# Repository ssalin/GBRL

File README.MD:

Documentation for Airquality platform can be found here

https://docs.google.com/document/d/1oFnARjLuFHp-5nVdnFOoGYGBi9iJlXXOtEU-Aas6cns/edit?usp=sharing

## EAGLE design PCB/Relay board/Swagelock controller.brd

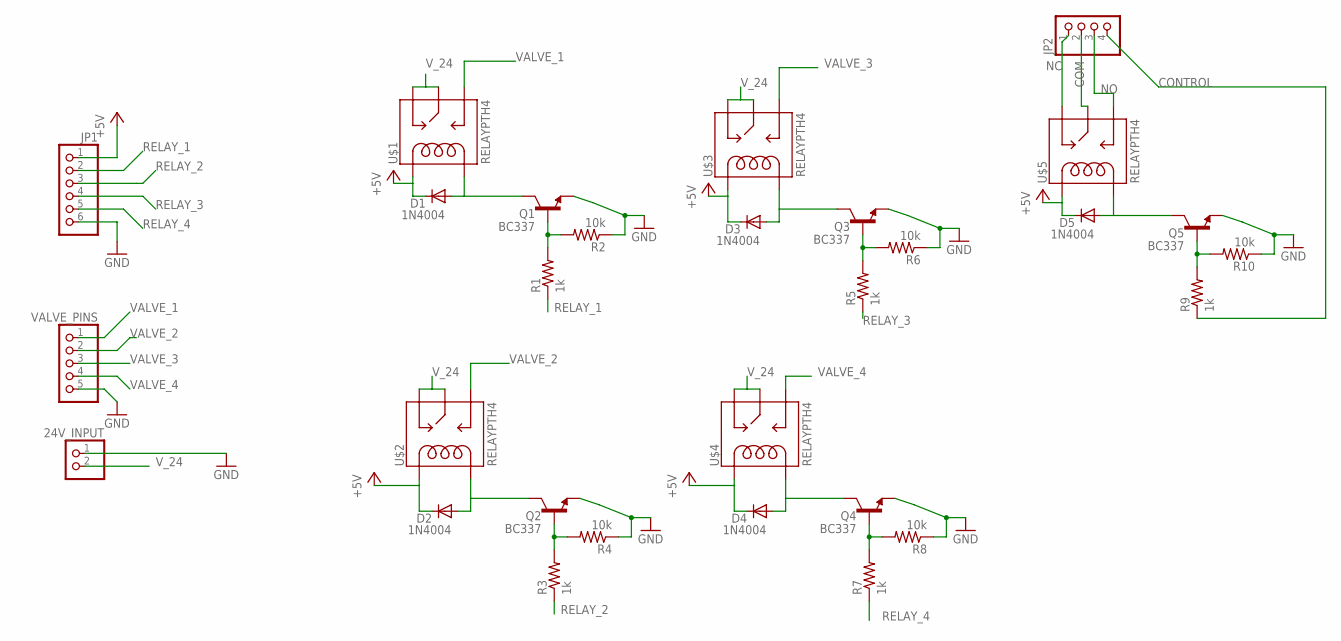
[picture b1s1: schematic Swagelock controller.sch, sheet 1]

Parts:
24V_INPUT: PINHD-1X2; 1X02
D1, D2, D3, D4, D5: 1N4004; DO41-10
JP1: PINHD-1X6; 1X06
JP2: PINHD-1X4; 1X04
Q1, Q2, Q3, Q4, Q5: BC337; TO92
R1, R3, R5, R7, R9: 1k; 0204/5
R2, R4, R6, R8, R10: 10k; 0204/5
U$1, U$2, U$3, U$4, U$5: RELAYPTH4; RELAY-JZC
VALVE_PINS: PINHD-1X5; 1X05

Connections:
+5V: D1.C, D2.C, D3.C, D4.C, D5.C, JP1.1, U$1.5 (COIL1), U$2.5 (COIL1), U$3.5 (COIL1), U$4.5 (COIL1), U$5.5 (COIL1)
COM: JP2.2, U$5.4 (MAIN)
CONTROL: JP2.4, R9.1
GND: 24V_INPUT.1, JP1.6, Q1.1 (E), Q2.1 (E), Q3.1 (E), Q4.1 (E), Q5.1 (E), R2.1, R4.1, R6.1, R8.1, R10.1, VALVE_PINS.5
unnamed: Q1.2 (B), R1.2, R2.2
unnamed: D1.A, Q1.3 (C), U$1.1 (COIL2)
unnamed: Q2.2 (B), R3.2, R4.2
unnamed: D2.A, Q2.3 (C), U$2.1 (COIL2)
unnamed: Q3.2 (B), R5.2, R6.2
unnamed: D3.A, Q3.3 (C), U$3.1 (COIL2)
unnamed: Q4.2 (B), R7.2, R8.2
unnamed: D4.A, Q4.3 (C), U$4.1 (COIL2)
unnamed: Q5.2 (B), R9.2, R10.2
unnamed: D5.A, Q5.3 (C), U$5.1 (COIL2)
NC: JP2.1, U$5.2 (NC)
NO: JP2.3, U$5.3 (NO)
RELAY_1: JP1.2, R1.1
RELAY_2: JP1.3, R3.1
RELAY_3: JP1.4, R5.1
RELAY_4: JP1.5, R7.1
VALVE_1: U$1.3 (NO), VALVE_PINS.1
VALVE_2: U$2.3 (NO), VALVE_PINS.2
VALVE_3: U$3.3 (NO), VALVE_PINS.3
VALVE_4: U$4.3 (NO), VALVE_PINS.4
V_24: 24V_INPUT.2, U$1.2 (NC), U$1.4 (MAIN), U$2.2 (NC), U$2.4 (MAIN), U$3.2 (NC), U$3.4 (MAIN), U$4.2 (NC), U$4.4 (MAIN)

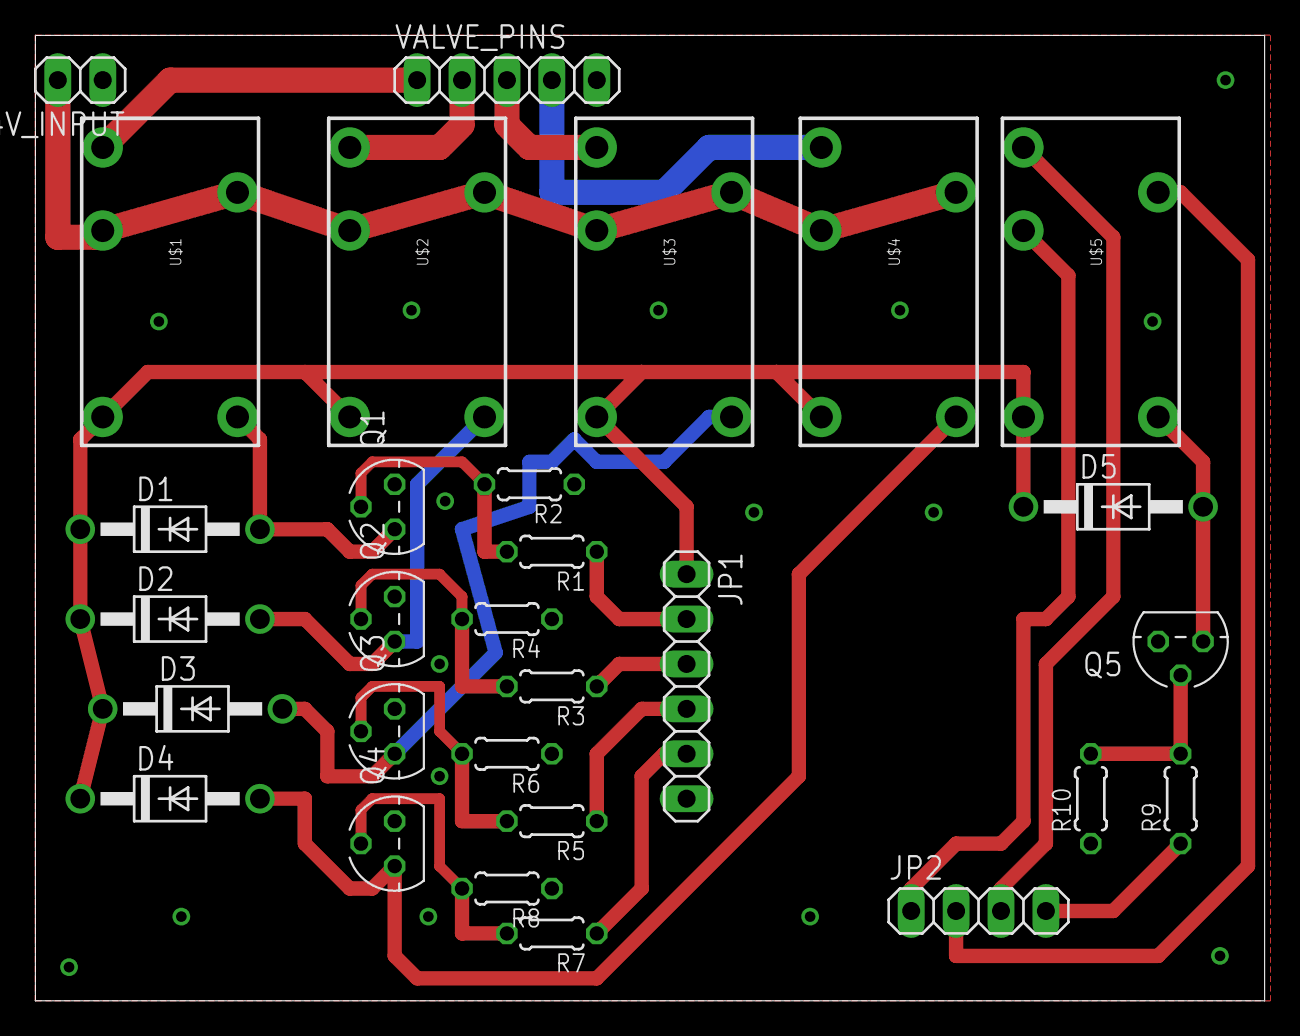
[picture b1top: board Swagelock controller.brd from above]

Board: 2 copper layers, 69.5 x 54.6 mm, 29 parts (0 on the bottom side), 25 nets.

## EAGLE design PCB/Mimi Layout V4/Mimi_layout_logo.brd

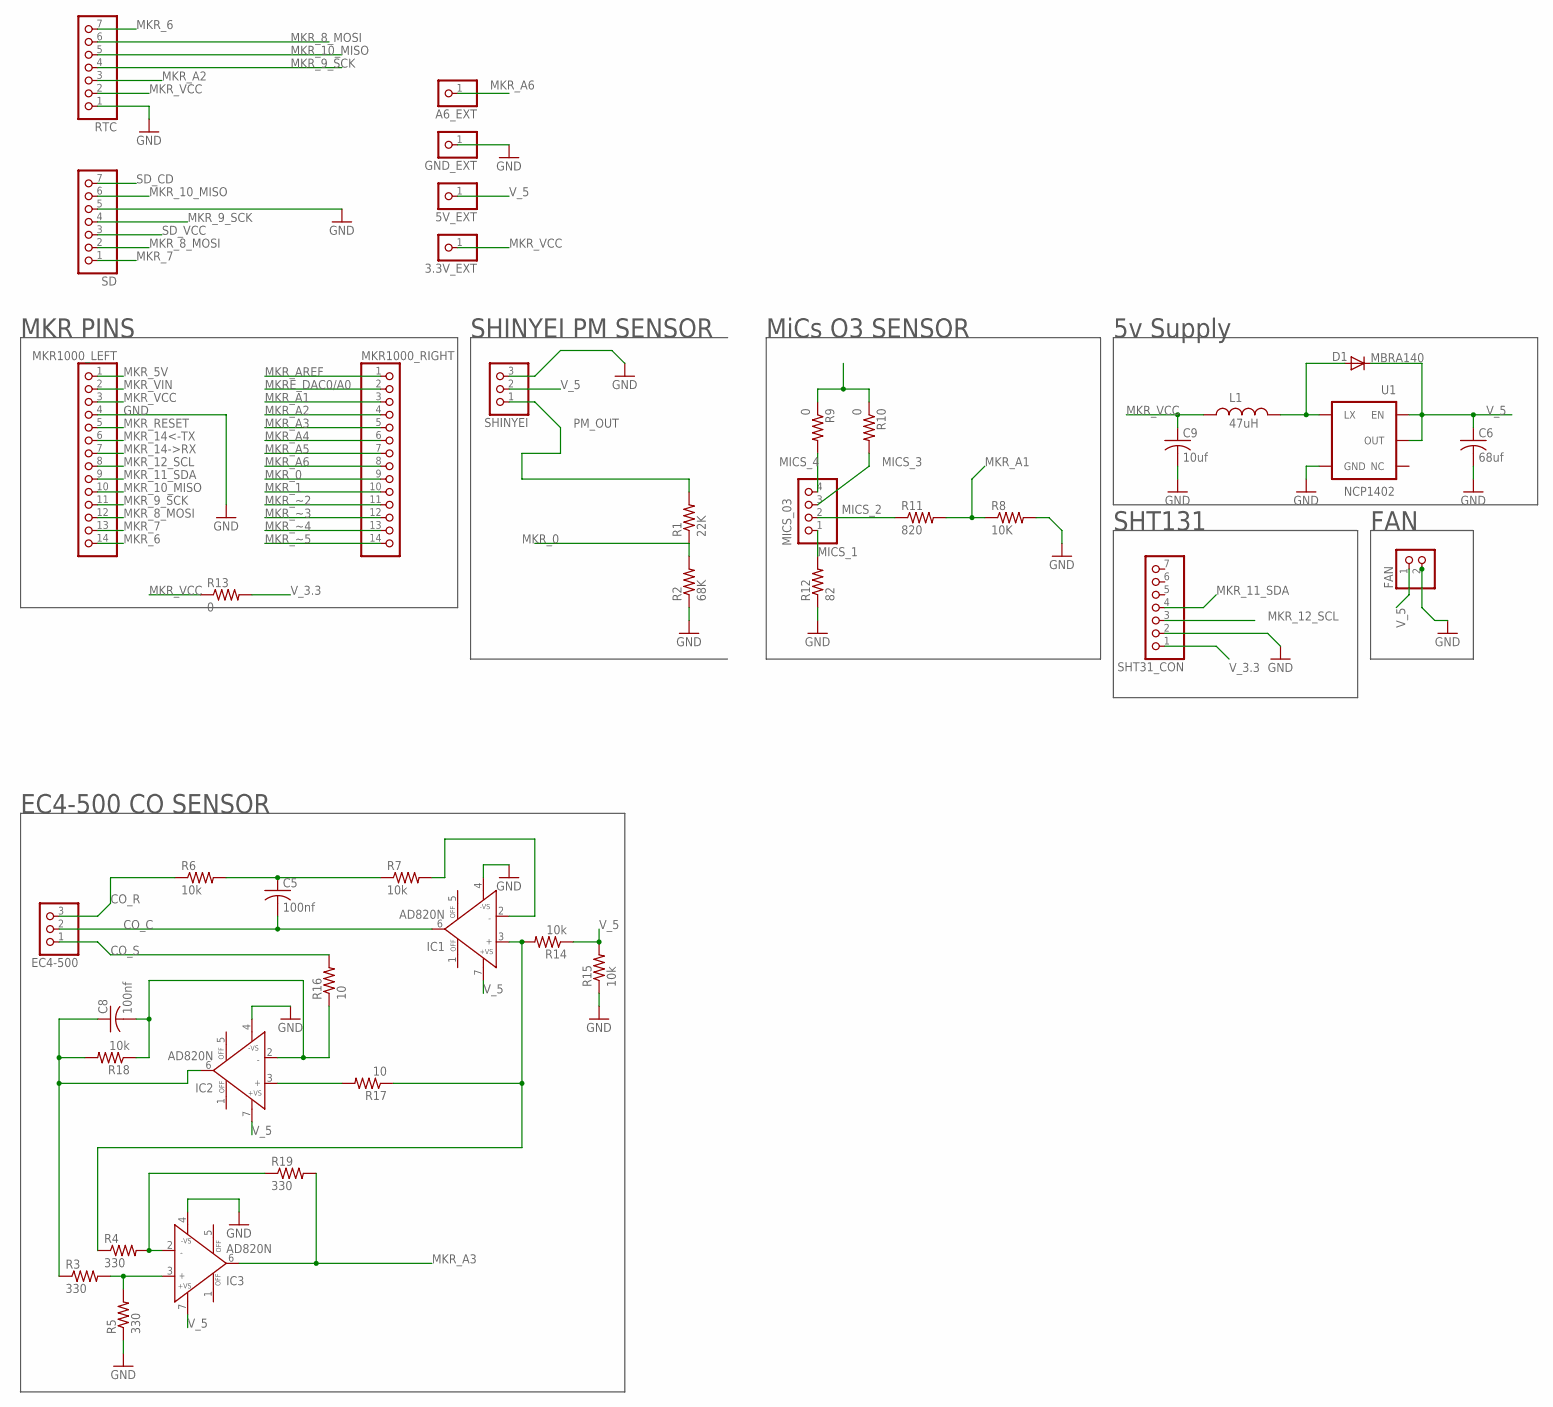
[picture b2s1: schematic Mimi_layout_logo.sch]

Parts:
3.3V_EXT, 5V_EXT: PINHD-1X1; 1X01
A6_EXT: PINHD-1X1; 1X01
C5, C8: 100nf; C0805
C6: 68uf; C0805
C9: 10uf; C0805
D1: MBRA140; SMA-DIODE
EC4-500: PINHD-1X3; 1X03
FAN: PINHD-1X2; 1X02
GND_EXT: PINHD-1X1; 1X01
IC1, IC2, IC3: AD820N; DIL08
L1: 47uH; CR54
MICS_03: PINHD-1X4; 1X04
MKR1000_LEFT, MKR1000_RIGHT: PINHD-1X14; 1X14
R1: 22K; R0805
R2: 68K; R0805
R3, R4, R5, R19: 330; R0805
R6, R7, R14, R15, R18: 10k; R0805
R8: 10K; R0805
R9, R10, R13: 0; R0805
R11: 820; R0805
R12: 82; R0805
R16, R17: 10; R0805
RTC: PINHD-1X7; 1X07
SD: PINHD-1X7; 1X07
SHINYEI: PINHD-1X3; 1X03
SHT31_CON: PINHD-1X7; 1X07
U1: NCP1402; SOT23-5

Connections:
CO_C: C5.2, EC4-500.2, IC1.6 (OUT)
CO_R: EC4-500.3, R6.1
CO_S: EC4-500.1, R16.2
GND: C6.2, C9.2, FAN.2, GND_EXT.1, IC1.4 (-VS), IC2.4 (-VS), IC3.4 (-VS), MKR1000_LEFT.4, R2.1, R5.1, R8.2, R12.1, R15.1, RTC.1, SD.5, SHINYEI.3, SHT31_CON.2, U1.4 (GND)
MICS_1: MICS_03.1, R12.2
MICS_2: MICS_03.2, R11.1
MICS_3: MICS_03.3, R10.2
MICS_4: MICS_03.4, R9.2
MKRE_DAC0/A0: MKR1000_RIGHT.2
MKR_0: MKR1000_RIGHT.9, R1.1, R2.2
MKR_1: MKR1000_RIGHT.10
MKR_5V: MKR1000_LEFT.1
MKR_6: MKR1000_LEFT.14, RTC.7
MKR_7: MKR1000_LEFT.13, SD.1
MKR_8_MOSI: MKR1000_LEFT.12, RTC.6, SD.2
MKR_9_SCK: MKR1000_LEFT.11, RTC.4, SD.4
MKR_10_MISO: MKR1000_LEFT.10, RTC.5, SD.6
MKR_11_SDA: MKR1000_LEFT.9, SHT31_CON.4
MKR_12_SCL: MKR1000_LEFT.8, SHT31_CON.3
MKR_14->RX: MKR1000_LEFT.7
MKR_14<-TX: MKR1000_LEFT.6
MKR_A1: MKR1000_RIGHT.3, R8.1, R11.2
MKR_A2: MKR1000_RIGHT.4, RTC.3
MKR_A3: IC3.6 (OUT), MKR1000_RIGHT.5, R19.2
MKR_A4: MKR1000_RIGHT.6
MKR_A5: MKR1000_RIGHT.7
MKR_A6: A6_EXT.1, MKR1000_RIGHT.8
MKR_AREF: MKR1000_RIGHT.1
MKR_RESET: MKR1000_LEFT.5
MKR_VCC: 3.3V_EXT.1, C9.1, L1.P$1 (1), MKR1000_LEFT.3, R13.1, RTC.2
MKR_VIN: MKR1000_LEFT.2
MKR_~2: MKR1000_RIGHT.11
MKR_~3: MKR1000_RIGHT.12
MKR_~4: MKR1000_RIGHT.13
MKR_~5: MKR1000_RIGHT.14
unnamed: D1.A, L1.P$2 (2), U1.5 (LX)
unnamed: C5.1, R6.2, R7.1
unnamed: IC1.3 (IN+), R4.1, R14.2, R17.1
unnamed: IC1.2 (IN-), R7.2
unnamed: IC2.3 (IN+), R17.2
unnamed: C8.2, IC2.2 (IN-), R16.1, R18.1
unnamed: C8.1, IC2.6 (OUT), R3.1, R18.2
unnamed: IC3.3 (IN+), R3.2, R5.2
unnamed: IC3.2 (IN-), R4.2, R19.1
PM_OUT: R1.2, SHINYEI.1
SD_CD: SD.7
SD_VCC: SD.3
V_3.3: R13.2, SHT31_CON.1
V_5: 5V_EXT.1, C6.1, D1.C, FAN.1, IC1.7 (+VS), IC2.7 (+VS), IC3.7 (+VS), R9.1, R10.1, R14.1, R15.2, SHINYEI.2, U1.1 (EN), U1.2 (OUT)

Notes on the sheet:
EC4-500 CO SENSOR
MiCs O3 SENSOR
SHINYEI PM SENSOR
MKR PINS
SHT131
FAN
5v Supply

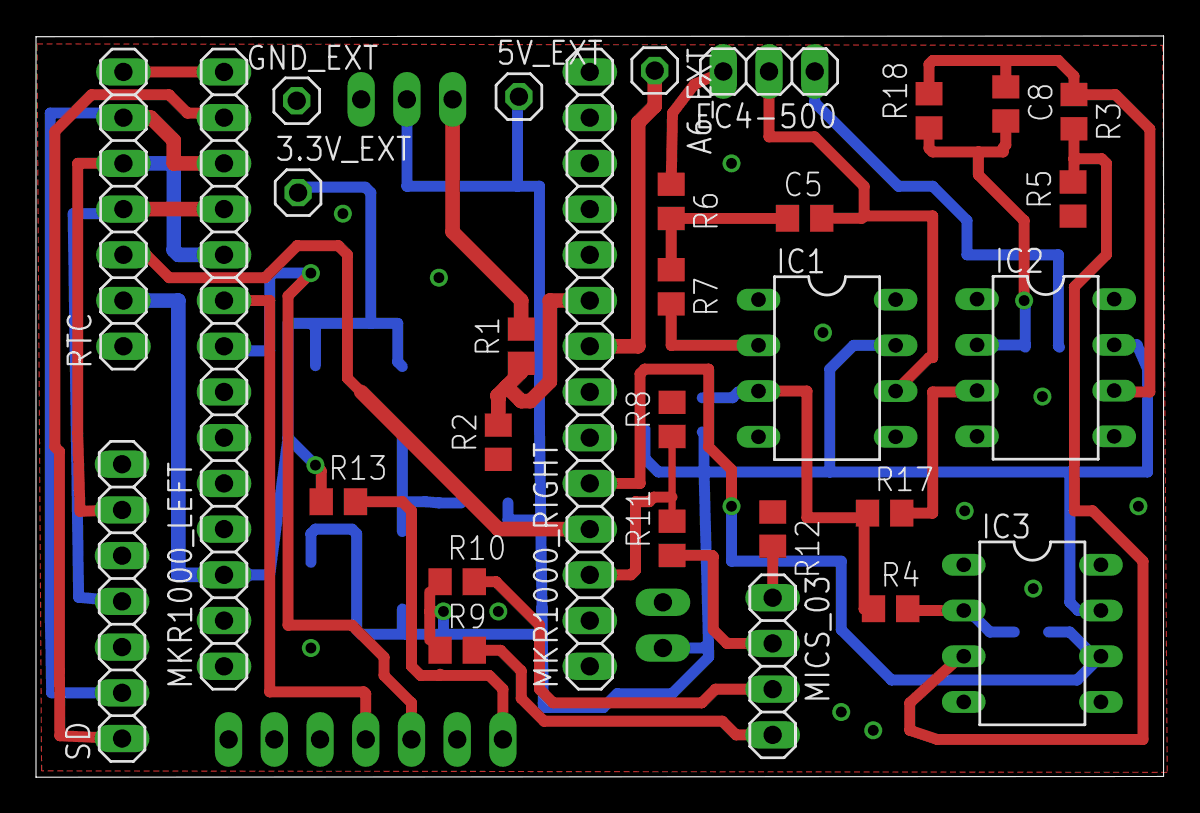
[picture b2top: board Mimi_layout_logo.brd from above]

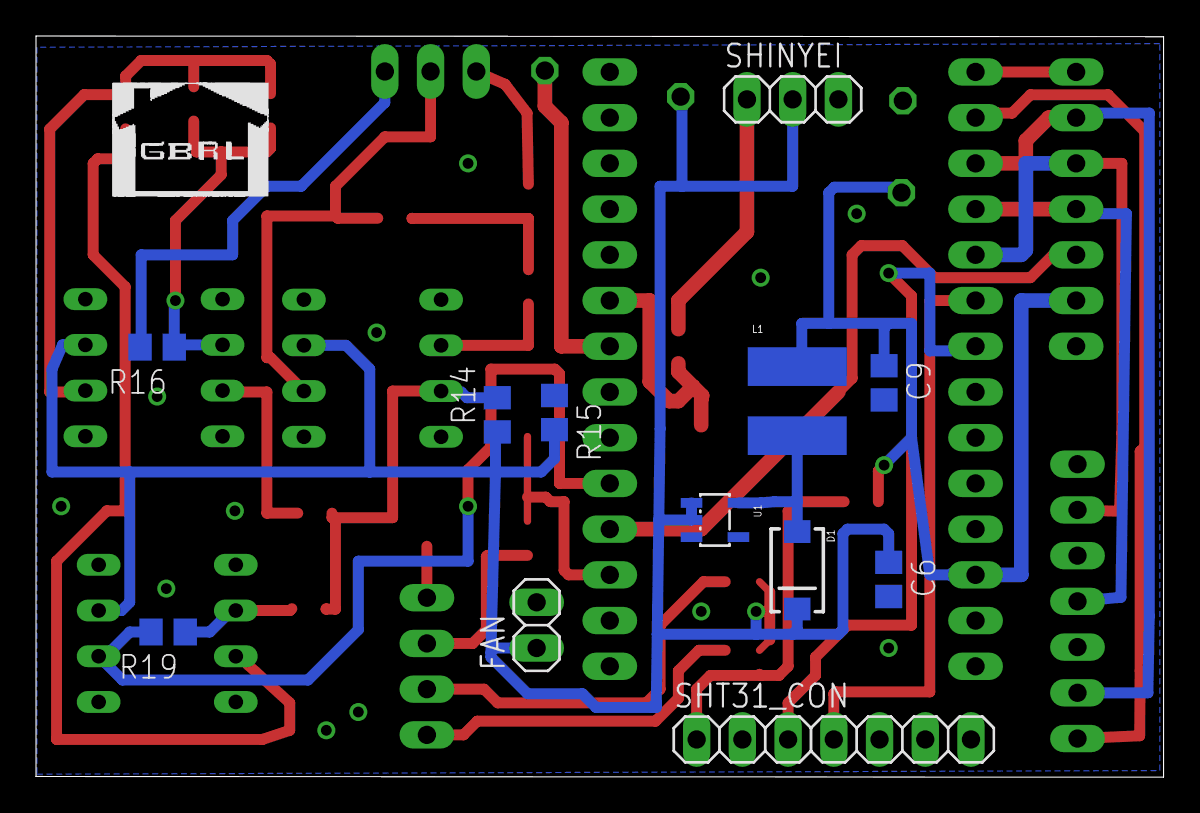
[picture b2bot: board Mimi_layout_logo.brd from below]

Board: 2 copper layers, 62.6 x 41.2 mm, 42 parts (12 on the bottom side), 33 nets.

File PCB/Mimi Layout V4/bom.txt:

Partlist

Exported from Mimi_layout.sch at 6/22/2017 7:39 PM

EAGLE Version 7.6.0 Copyright (c) 1988-2016 CadSoft

Assembly variant: 

Part          Value          Device               Package   Library        Sheet

C5            100nf          C-USC0805            C0805     resistor       1
C6            68uf           C-USC0805            C0805     resistor       1
C8            100nf          C-USC0805            C0805     resistor       1
C9            10uf           C-USC0805            C0805     resistor       1
D1            MBRA140        DIODESMA             SMA-DIODE SparkFun       1
EC4-500                      PINHD-1X3            1X03      pinhead        1
FAN                          PINHD-1X2            1X02      pinhead        1
IC1           AD820N         AD820N               DIL08     analog-devices 1
IC2           AD820N         AD820N               DIL08     analog-devices 1
IC3           AD820N         AD820N               DIL08     analog-devices 1
L1            47uH           INDUCTORCR54         CR54      SparkFun       1
MICS_03                      PINHD-1X4            1X04      pinhead        1
MKR1000_LEFT                 PINHD-1X14           1X14      pinhead        1
MKR1000_RIGHT                PINHD-1X14           1X14      pinhead        1
R1            22K            R-US_R0805           R0805     resistor       1
R2            68K            R-US_R0805           R0805     resistor       1
R3            330            R-US_R0805           R0805     resistor       1
R4            330            R-US_R0805           R0805     resistor       1
R5            330            R-US_R0805           R0805     resistor       1
R6            10k            R-US_R0805           R0805     resistor       1
R7            10k            R-US_R0805           R0805     resistor       1
R8            10K            R-US_R0805           R0805     resistor       1
R9            0              R-US_R0805           R0805     resistor       1
R10           0              R-US_R0805           R0805     resistor       1
R11           820            R-US_R0805           R0805     resistor       1
R12           82             R-US_R0805           R0805     resistor       1
R13           0              R-US_R0805           R0805     resistor       1
R14           10k            R-US_R0805           R0805     resistor       1
R15           10k            R-US_R0805           R0805     resistor       1
R16           10             R-US_R0805           R0805     resistor       1
R17           10             R-US_R0805           R0805     resistor       1
R18           10k            R-US_R0805           R0805     resistor       1
R19           330            R-US_R0805           R0805     resistor       1
SHINYEI                      PINHD-1X3            1X03      pinhead        1
SHT31_CON                    PINHD-1X7            1X07      pinhead        1
U1            NCP1402        V_REG_NCP1400SOT23-5 SOT23-5   SparkFun       1

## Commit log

2017-07-12 added layouts
    added layout and schematic for Swagelock valve controller & MimiV4
2017-07-12 cleaned up junk files
2017-07-12 added v1 of code
2017-07-12 Updates, Valve controller
    Updated V1 to V2
    Added Swagelock control code
2017-07-12 Namechange
    to keep arduino software happy
2017-07-12 Functions
    sensor code more function-oriented and therefore more modular
2017-07-12 Many Changes
    Cleaned up code - more modular (many function calls), better commenting,
    clearer seperation of definitions, includes, globals, and functions.
    Also began implimenting SD logging functionality
2017-07-12 finished SD
    finished adding what seems like it should manage the SD card, hopefully
    it auto-appends to existing files. will need to do some tests to make
    sure behavior is as expected.
2017-07-12 Consistancy
    better consistancy. removed all const <type> and replaced with #defines
    allowing easier modification since value only need to be changed in one
    place.
2017-07-12 Datestamping
    Device should now log data with time/date information. code is also
    primed for IRQs
2017-07-14 small fix
    removed delay since RTC will handle delays
2017-08-29 updated V2 to V3
2017-08-29 Bugfixes
    Program now writes to SD card more than once when wifi is turned on!
    wifi always connects/disconnects when posting
2017-09-01 cleanup
    cleaned up code a bit, making baby steps towards getting sleep mode working
2017-09-06 Program used to debug standby mode
    I was having issues with the libraries that let the MKR1000 enter standby mode had to build this program with a blinking LED to figure out if IRQs were firing correctly / make them fire correctly. wi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
2017-09-07 Fixed Sleep (Sorta)
    Sleep kinda works now. for some reason the interrupts are getting triggered every minute or so - trying to figure out what's causing them to happen. Might need to clear alarm 2?
2017-09-14 Debugging
    still debugging sleep issues. moved function calls around to minimize the number of frames on the stack. program currently hangs when reconnecting to wifi the third time. not a full hang, just can't 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
2017-09-14 Timechange fix?
    Tried to fix an issue where the device would not wake up when the hour changed.
2017-09-26 bugfixes
    tried to add a way to reset the program if it get's deadlocked via alarm2. not sure if that is functioning but did make it so interrupts from the RTC are used to wait regardless of low power mode or 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
2017-09-28 Add files via upload
    Switched to builtin LED to reduce external apparati needed for debugging.
    tried some timing changes but the double-posting doesnt seem to be effected.
2017-10-10 fixed IRQ never wakeup
    fixed a bug where the device would never get out of the IRQ wait loop. this also should fix the never-wake-up bug experienced in low power mode.
2017-10-12 cleaning up dir structure
    cleanup
2017-10-12 LP fix, API changes
    Lowpower mode seems to work without wifi enabled. changed the API to add a few parameters, changed naming, made order better
2017-12-06 LoRa
    Added LoRa code
    TTN_TEST_1 was just to send hello world
    TTN_TEST_2 sends data
    TTN_TEST_3 sleeps
    Data transmission is pretty inconsistent for some reason.
2018-01-13 changed SPI speed
    Altering the SPI speed seems to have reduced the connectivity issues. now 10-20% of packets getting through
2018-01-13 updates & fixes
    added CO2 & SM50, better shinyei reading
2018-01-17 Update AQmonitorV4.ino
    removed some networking information
2018-01-18 Serial connection fix
    removed line causing code to wait for a serial connection, which was used to debug SPI speed problems
2018-01-18 Serial fix
    removed line causing code to wait for a serial connection, which was used to debug SPI speed problems
2018-01-22 added SD logging to LoRa
    OTAA for DEV_2 with SD logging of every "sent" packet for reliability data
2018-02-12 added stable code for Dev1, Dev2
    doesn't send PM or CO, easy to fix via uncommenting if they are desired. stopped sending because readings were noise.
2018-02-12 SD test program
    Program to make sure SD care is present and formatted correctly
2018-02-12 Ozone Converter
    Program to convert 3.3v logic level ADC readings to an ozone concentration based on the SM50 devices in the lab

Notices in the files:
parts and their libraries:
SparkFun-Aesthetics: Licensing: Creative Commons ShareAlike 4.0 International - https://creativecommons.org/licenses/by-sa/4.0
